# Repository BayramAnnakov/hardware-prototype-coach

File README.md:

# Hardware Prototype Coach

A skill for a coding agent (Claude Code, Codex and similar) that helps a person with no hardware experience invent a physical object they want, see it, get editable CAD, test one real physical constraint, change one thing and see what breaks, and leave with an honest record of what exists.

It was made for a 50-minute session of the AI Natives meetup on 18 November 2026. No parts and no 3D printer are needed. The idea for the session came from Anthropic's write-up on [electronics design with Claude](https://www.anthropic.com/research/claude-electronics-design).

## Use it

1. Clone this repository and open a new agent session in its folder. The agent needs to create files and run Python.
2. Paste this, and add your idea if you have one:

```text
Read skills/hardware-prototype-coach/SKILL.md and use that process to help
me invent and make my own digital prototype of a physical object. I am new
to hardware design. We have about 50 minutes. Start with a short
conversation about what I would like to make. If I do not know yet, help me
choose an idea. Show visual concepts first and help me find an object that
I want to make. Do not go straight to CAD. Create files in the folder
my-prototype.
```

[START-HERE.md](START-HERE.md) is the participant handout, in Russian, with the same prompt.

## What is inside

- `skills/hardware-prototype-coach/SKILL.md` - the process the agent follows.
- `skills/hardware-prototype-coach/references/` - tool recipes (CadQuery, Diode `pcb`, quick physical estimates, images from an image API, an interactive model page), redesign cards, the step from checked CAD to a printable sample, fabrication options, parts and power (real envelopes, pin and bus budget, runtime, heat), and a bill of materials with cost.
- `reference/` - a finished example, a desk timer: enclosure source, STEP and STL exports, a small circuit, a behaviour replay and its passport.

## What it does and does not establish

The skill separates these outcomes and asks the agent to say which one was reached: CAD was generated; geometry was checked; a circuit compiled; a layout was routed; behaviour was replayed; a service quoted the files; a physical object was built and tested.

Everything in this repository stops before the last one. The checks are computed on declared volumes and simple estimates. They are not a physical test, a simulation or a manufacturability review.

## Status

The skill was rehearsed with two agents on macOS and run once end to end on a real idea, through a printable sample and an instant quote from a print service. Lessons from that run are in the references. Windows was not tested. Service capabilities and prices in `references/fabrication.md` carry the date they were read and will go stale.

## License

MIT. See [LICENSE](LICENSE).

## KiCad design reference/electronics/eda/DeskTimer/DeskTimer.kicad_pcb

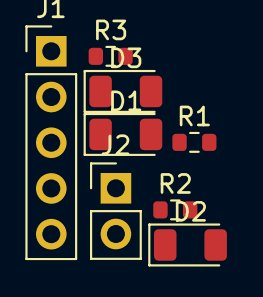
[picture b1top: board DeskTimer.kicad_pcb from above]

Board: 2 copper layers, 8 parts (0 on the bottom side), 8 nets, no tracks yet.

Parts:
D1: LED RED; LED_1206_3216Metric
D2: LED AMBER; LED_1206_3216Metric
D3: LED GREEN; LED_1206_3216Metric
J1: 2.54mm 5 x 1 THT Vertical Male; PinHeader_1x05_P2.54mm_Vertical
J2: 2.54mm 2 x 1 THT Vertical Male; PinHeader_1x02_P2.54mm_Vertical
R1, R2, R3: 1k; R_0603_1608Metric

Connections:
D0_RED: J1.1, R1.1
D1_AMBER: J1.2, R2.1
D2_GREEN: J1.3, R3.1
D3_BUTTON: J1.4, J2.1
GND: D1.1, D2.1, D3.1, J1.5, J2.2
LED_AMBER_A: D2.2, R2.2
LED_GREEN_A: D3.2, R3.2
LED_RED_A: D1.2, R1.2
